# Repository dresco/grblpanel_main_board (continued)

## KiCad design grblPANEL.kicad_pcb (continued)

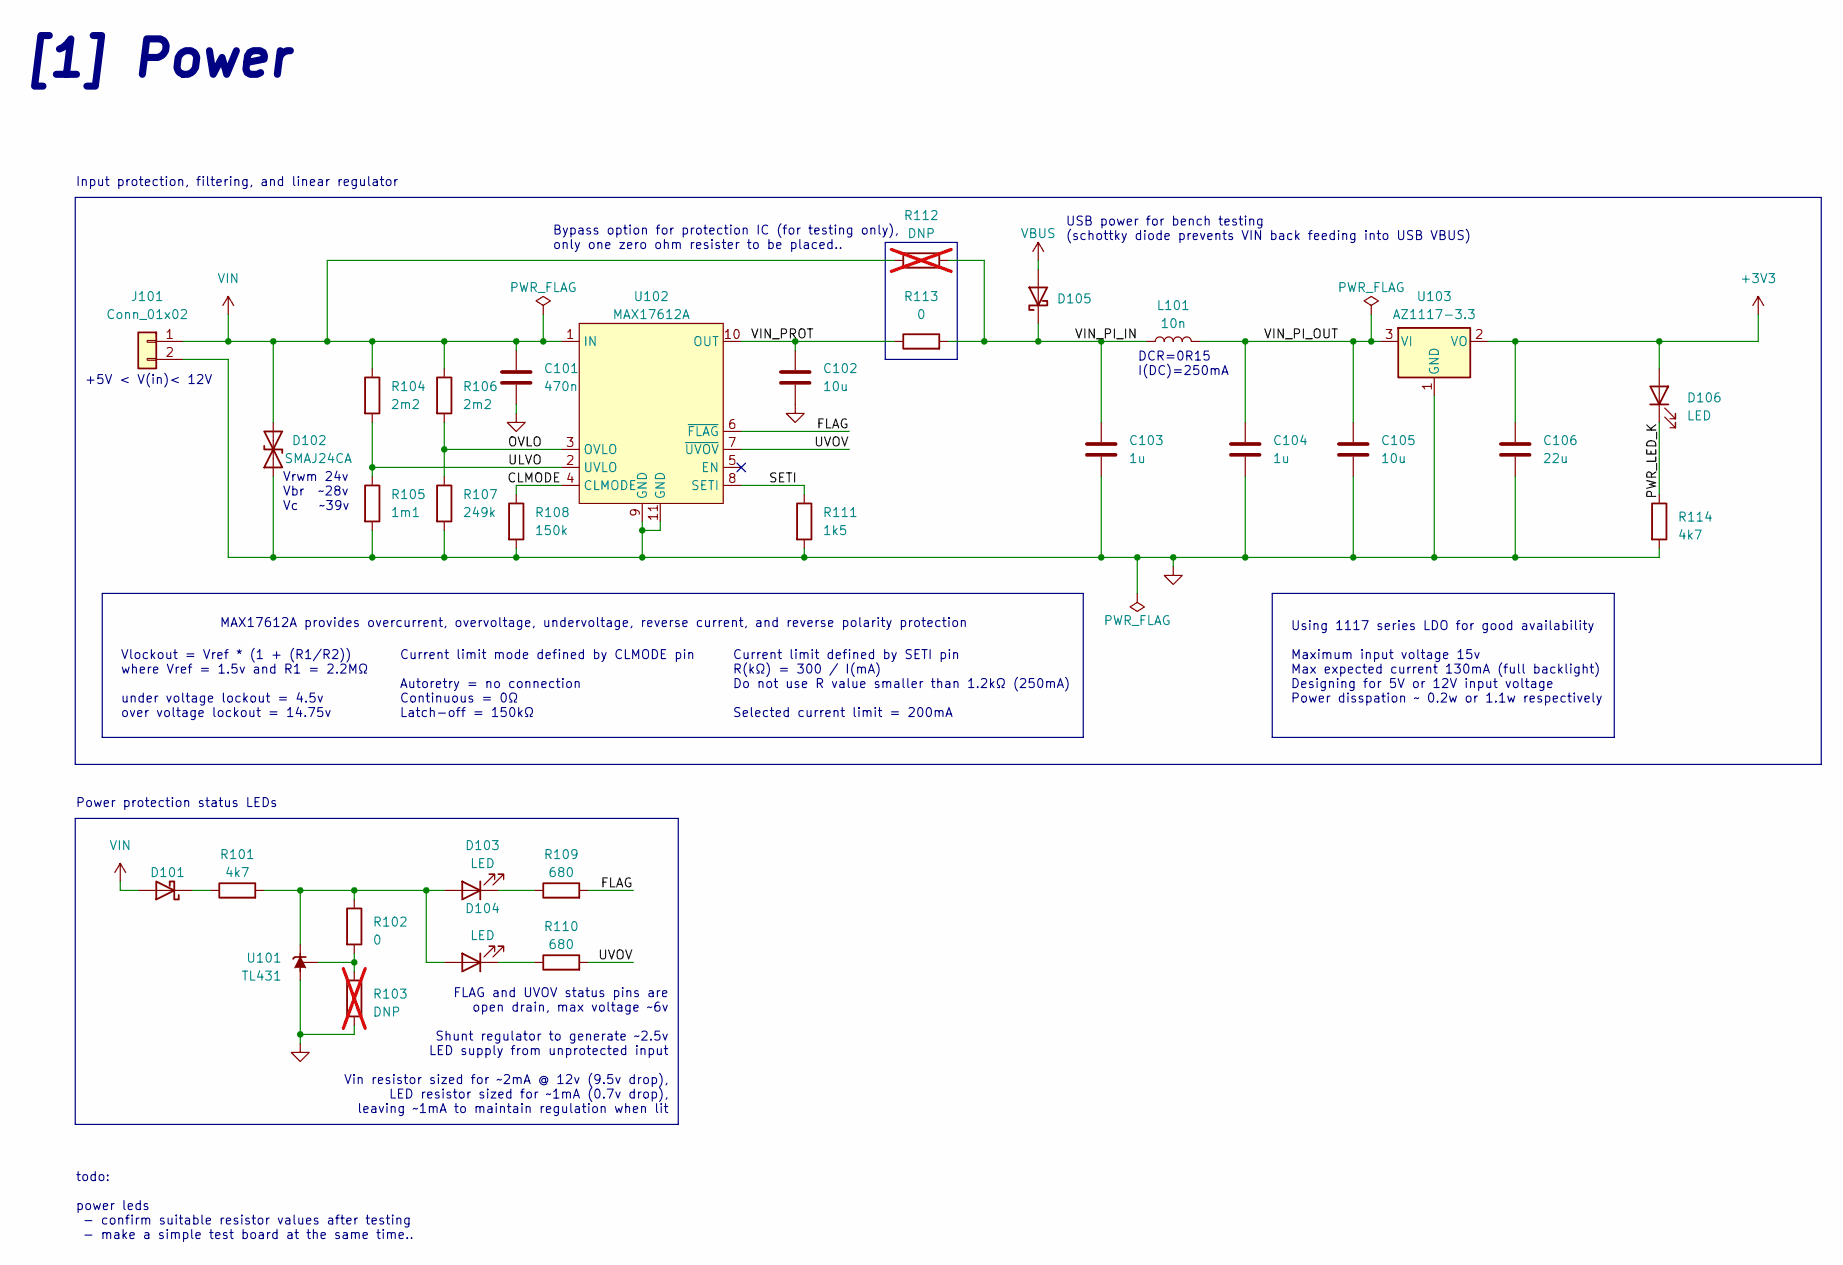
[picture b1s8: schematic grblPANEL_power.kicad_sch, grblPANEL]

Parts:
C101: 470n; C_0805_2012Metric
C102, C105: 10u; C_0805_2012Metric
C103, C104: 1u; C_0603_1608Metric
C106: 22u; C_0805_2012Metric
D101, D105: D_Schottky; D_SOD-323
D102: SMAJ24CA; D_SMA
D103, D104, D106: LED; LED_0603_1608Metric
J101: Conn_01x02; TerminalBlock_Phoenix_PT-1,5-2-3.5-H_1x02_P3.50mm_Horizontal
L101: 10n; L_0603_1608Metric
R101, R114: 4k7; R_0603_1608Metric
R102, R113: 0; R_0603_1608Metric
R103, R112: DNP; R_0603_1608Metric; not fitted
R104, R106: 2m2; R_0603_1608Metric
R105: 1m1; R_0603_1608Metric
R107: 249k; R_0603_1608Metric
R108: 150k; R_0603_1608Metric
R109, R110: 680; R_0603_1608Metric
R111: 1k5; R_0603_1608Metric
U101: TL431; SOT-23
U102: MAX17612A; TDFN-10-1EP_3x3mm_P0.5mm_EP1.6x2.39mm_ThermalVias
U103: AZ1117-3.3; SOT-223-3_TabPin2

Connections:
+3V3: C106.1, D106.2 (A), U103.2 (VO); also elsewhere on the board
/Power/CLMODE: R108.1, U102.4 (CLMODE)
/Power/FLAG: R109.2, U102.6 (~FLAG)
/Power/OVLO: R106.2, R107.1, U102.3 (OVLO)
/Power/PWR_LED_K: D106.1 (K), R114.1
/Power/SETI: R111.1, U102.8 (SETI)
/Power/ULVO: R104.2, R105.1, U102.2 (UVLO)
/Power/UVOV: R110.2, U102.7 (~UVOV)
/Power/VIN_PI_IN: C103.1, D105.1 (K), L101.1, R112.2, R113.2
/Power/VIN_PI_OUT: C104.1, C105.1, L101.2, U103.3 (VI)
/Power/VIN_PROT: C102.1, R113.1, U102.10 (OUT)
GND: C101.2, C102.2, C103.2, C104.2, C105.2, C106.2, D102.1 (A1), J101.2, R103.2, R105.2, R107.2, R108.2, R111.2, R114.2, U101.3 (A), U102.9 (GND), U102.11 (GND), U103.1 (GND); also elsewhere on the board
unnamed: D101.1 (K), R101.1
unnamed: D103.2 (A), D104.2 (A), R101.2, R102.1, U101.1 (K)
unnamed: D103.1 (K), R109.1
unnamed: D104.1 (K), R110.1
unnamed: R102.2, R103.1, U101.2 (REF)
VBUS: D105.2 (A); also elsewhere on the board
VIN: C101.1, D101.2 (A), D102.2 (A2), J101.1, R104.1, R106.1, R112.1, U102.1 (IN)

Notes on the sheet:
+5V < V(in)< 12V
USB power for bench testing (schottky diode prevents VIN back feeding into USB VBUS)
Using 1117 series LDO for good availability Maximum input voltage 15v Max expected current 130mA (full backlight) Designing for 5V or 12V input voltage Power disspation ~ 0.2w or 1.1w respectively
MAX17612A provides overcurrent, overvoltage, undervoltage, reverse current, and reverse polarity protection
Input protection, filtering, and linear regulator
FLAG and UVOV status pins are open drain, max voltage ~6v Shunt regulator to generate ~2.5v LED supply from unprotected input Vin resistor sized for ~2mA @ 12v (9.5v drop), LED resistor sized for ~1mA (0.7v drop), leaving ~1mA to maintain regulation when lit
Bypass option for protection IC (for testing only), only one zero ohm resister to be placed..
Current limit defined by SETI pin R(kΩ) = 300 / I(mA) Do not use R value smaller than 1.2kΩ (250mA) Selected current limit = 200mA
Power protection status LEDs
Vrwm 24v Vbr ~28v Vc ~39v
[1] Power
Current limit mode defined by CLMODE pin Autoretry = no connection Continuous = 0Ω Latch-off = 150kΩ
Vlockout = Vref * (1 + (R1/R2)) where Vref = 1.5v and R1 = 2.2MΩ under voltage lockout = 4.5v over voltage lockout = 14.75v
DCR=0R15 I(DC)=250mA
todo: power leds - confirm suitable resistor values after testing - make a simple test board at the same time..

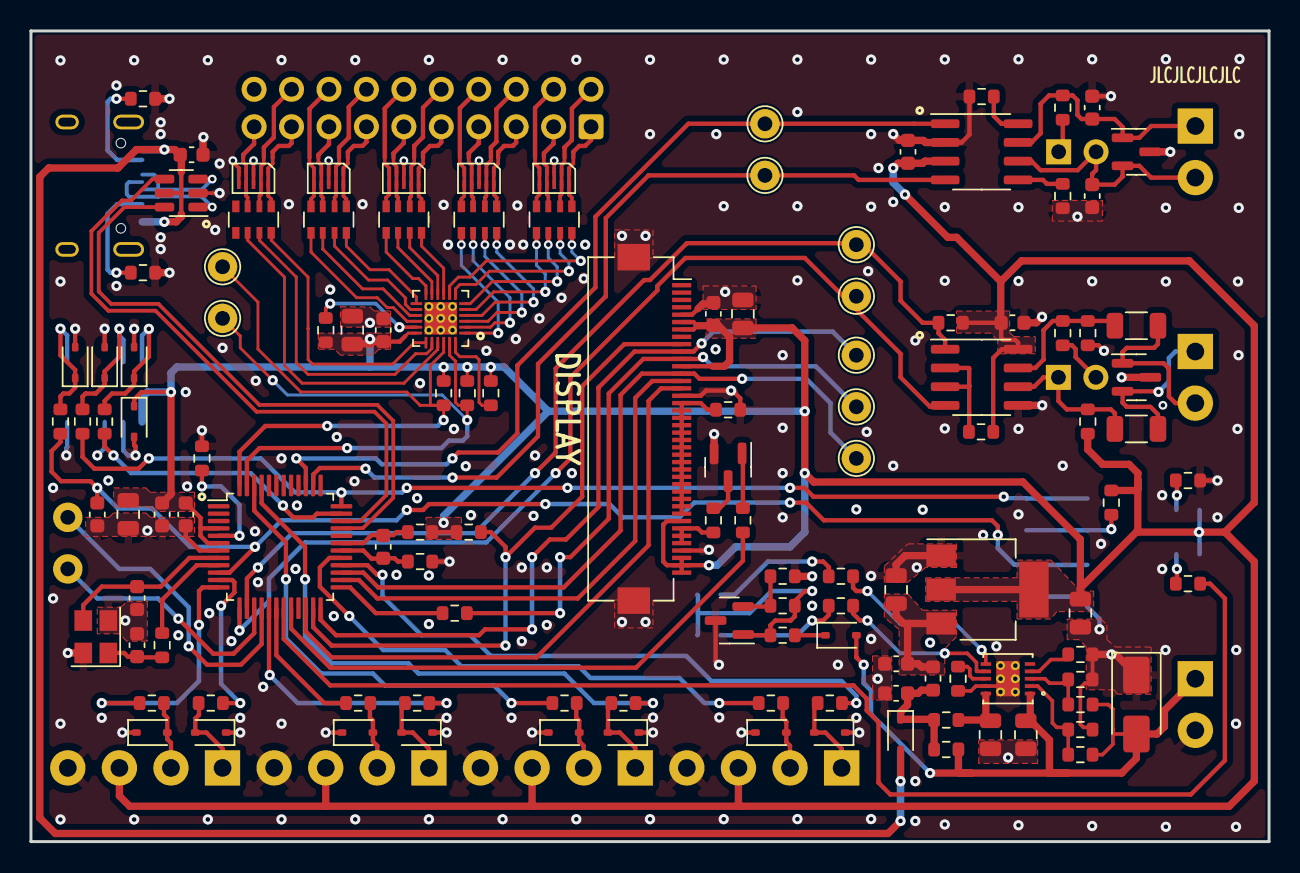
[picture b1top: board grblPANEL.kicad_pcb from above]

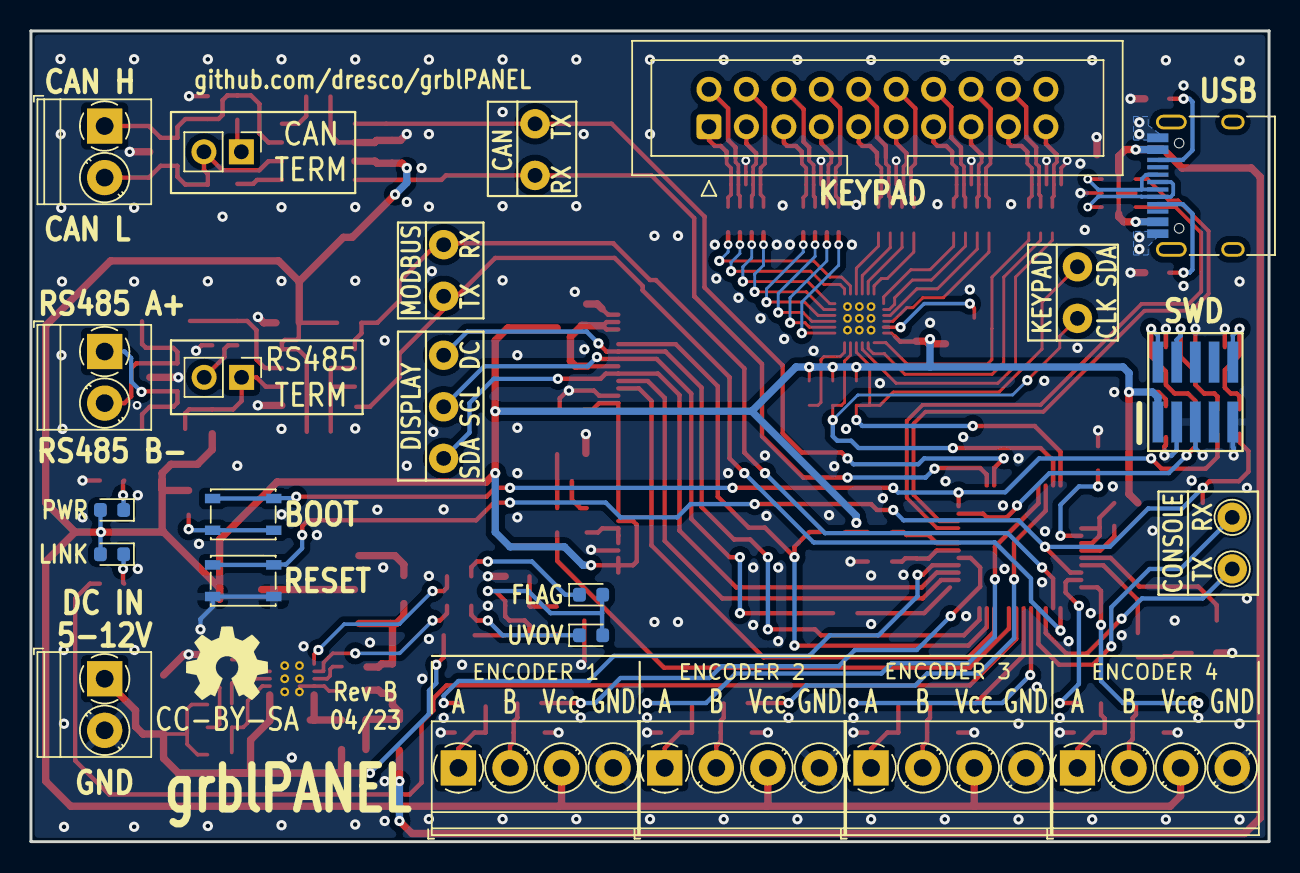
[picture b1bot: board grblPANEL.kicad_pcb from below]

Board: 4 copper layers, 84.0 x 55.0 mm, 142 parts (20 on the bottom side), 127 nets.

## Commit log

2022-12-09 ERC fixes
2022-12-16 Refresh
2022-12-16 Status LED & annotation cleanup
2022-12-16 Weeny schematic update
2022-12-16 Initial PCB setup & rules
2022-12-20 PCB layout - WIP
2022-12-22 WIP layout
2022-12-22 Resistor & TVS arrays
2023-01-03 1st stab at routing power input section
2023-01-03 1st stab at routing can interface
2023-01-03 1st stab at modbus interface routing
2023-01-04 1st stab at keypad + usb routing
2023-01-04 bit more usb..
2023-01-06 some mcu..
2023-01-06 1st crack at display routing
2023-01-06 modbus cleanup
2023-01-07 power section cleanup change 1206 caps to 0805
2023-01-07 reset & bootloader buttons
2023-01-08 more routing
2023-01-08 bit more routing buttons etc
2023-01-08 initial routing complete, pending test points & cleanup
2023-01-08 Ensure silkscreen is not covering holes
2023-01-17 small cleanups
2023-01-17 place gnd vias near all signal and power vias
2023-01-17 sheet 1 test points
2023-01-17 canbus & modbus test points
2023-01-17 keypad test points
2023-01-17 stiching vias
2023-01-17 arrange fab layer text
2023-01-17 Back side silkscreen - labels etc..
2023-01-17 bit more silkscreen
2023-01-18 jlc placement text
2023-01-18 silkscreen - id pin 1 where missing
2023-01-18 bit more silk
2023-01-18 add thermal relief to internal ground planes
2023-01-18 set zone priority of power puddles
2023-01-18 outer layer ground pour and custom rule
    needs additional custom rule to prevent the
    ground pour from inheriting the tigher clearances
    from erlier custom rules (as zone is within affected
    courtyards)
    note weird interactions with GND power puddles if adding
    thermal reliefs
2023-01-18 remove outer pours..
    ..while considering what to do about the power puddles
2023-01-18 output settings for jlcpcb
2023-01-19 Add Rev A manufacturing files
2023-01-19 Add mounting pads to ILI9488 connector symbol
    Tied to ground plane in schematic and pcb
2023-01-19 tweak ILI9488 mounting pads
    add copper pour to bottom layer
2023-01-19 Updated Rev A manufacturing files
    Copper pours on outer layers
2023-02-11 v7 upgrade
    Schematic symbols updated from libraries
2023-02-11 v7 upgrade
    pcb editor
    update from schematic
    update footprints from library
    board setup, thermal relief count
    still DRC warnings where symbols have been updated locally with 3d
    models etc
2023-03-06 Move keypad connector & protection
    Will facilitate screen connector move
2023-03-06 Move display connector
    Moved 2.7mm towards board edge to take some strain off the flex
    connector. (As far as it can go before courtyard violation).
2023-03-06 Minor tidy up..
2023-03-06 Schematic: add usart6 connector on pa4/pa5
2023-03-06 Power protection status LEDs - wip
2023-03-09 More power protect status LED work
2023-03-09 Import changes from schematic
    not yet placed/routed
2023-04-24 Place and route changes from schematic
    Headers for serial console.
    DNP components to v7 format.
    Power status components.
    LEDs to bottom side, plus silkscreen.
2023-04-28 Update schematic page settings (RevB)
2023-04-28 Update PCB page settings (RevB)
2023-04-28 Silkscreen & test point tweaks
2023-04-28 Increase 0.25/0.55mm vias to 0.30/0.60mm
    (JLC price bump for 0.25 drill holes)
2023-04-28 Final tweaks before submitting
2023-04-28 RevB manufacturing files
2023-06-08 v7 upgrade
    schematic symbols updated from libraries
    pcb update from schematic
    update footprints from library
    board setup, thermal relief count
    still DRC warnings where symbols have been updated locally with 3d
    models etc
2023-06-08 Move display flex connector
    Move keypad connector & protection to create clearance.
    Moved display connector 2.7mm towards board edge to reduce strain
    on the flex connector.
    Minor tidy up..
2023-06-08 Schematic: add usart6 connector on pa4/pa5
    will be used for console log output
2023-06-08 Add power protection status LEDs
2023-06-08 Board changes for Rev B
    Import changes from schematic.
    Place and route changes from schematic:
    Headers for serial console.
    DNP components to v7 format.
    Power status components.
    LEDs to bottom side, plus silkscreen.
2023-06-08 Increase 0.25/0.55mm vias to 0.30/0.60mm
    (JLC price bump for 0.25 drill holes)
    Final tweaks before submitting
2023-06-08 Green LED resistor changes
    Reduce the intensity of the green status LEDs, resistors changed
    from 1k to 4k7
2023-06-10 Documentation updates
